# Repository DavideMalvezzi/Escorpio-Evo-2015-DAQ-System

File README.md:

# Introduction
Data Acquisition System realized for the prototype [Escorpio](https://www.facebook.com/TeamZeroCEscorpioEvo/?fref=ts) in 2015.

The DAQ System was realized to get real-time information from the prototype Escorpio during its races and visualize the data on a PC through
charts and widgets.

In the **HW** folder are placed the electronics boards realized with eagle. All the boards where controlled by an Arduino Due and placed inside 
the prototype.

In the **SW** folder are placed the software sources file:
- the Arduino Due software was in charge of collecting all the prototype data through the [Can Bus](https://en.wikipedia.org/wiki/CAN_bus) inside Escorpio and then to send the data 
to a remote PC using a [GSM SIM 900 module](http://www.geeetech.com/wiki/index.php/Arduino_GPRS_Shield);
- the remote PC was connected to another GSM SIM 900 module via USB and the software was in charge of controlling it, parse all the data 
coming from the other module and show it with charts and widgets. All the visualization views are completely personalizable thanks to the
user interface. All the data received is also saved in a local SQLite database.

All the code is C++, using [Qt Library](https://www.qt.io/developers/) for the PC software.

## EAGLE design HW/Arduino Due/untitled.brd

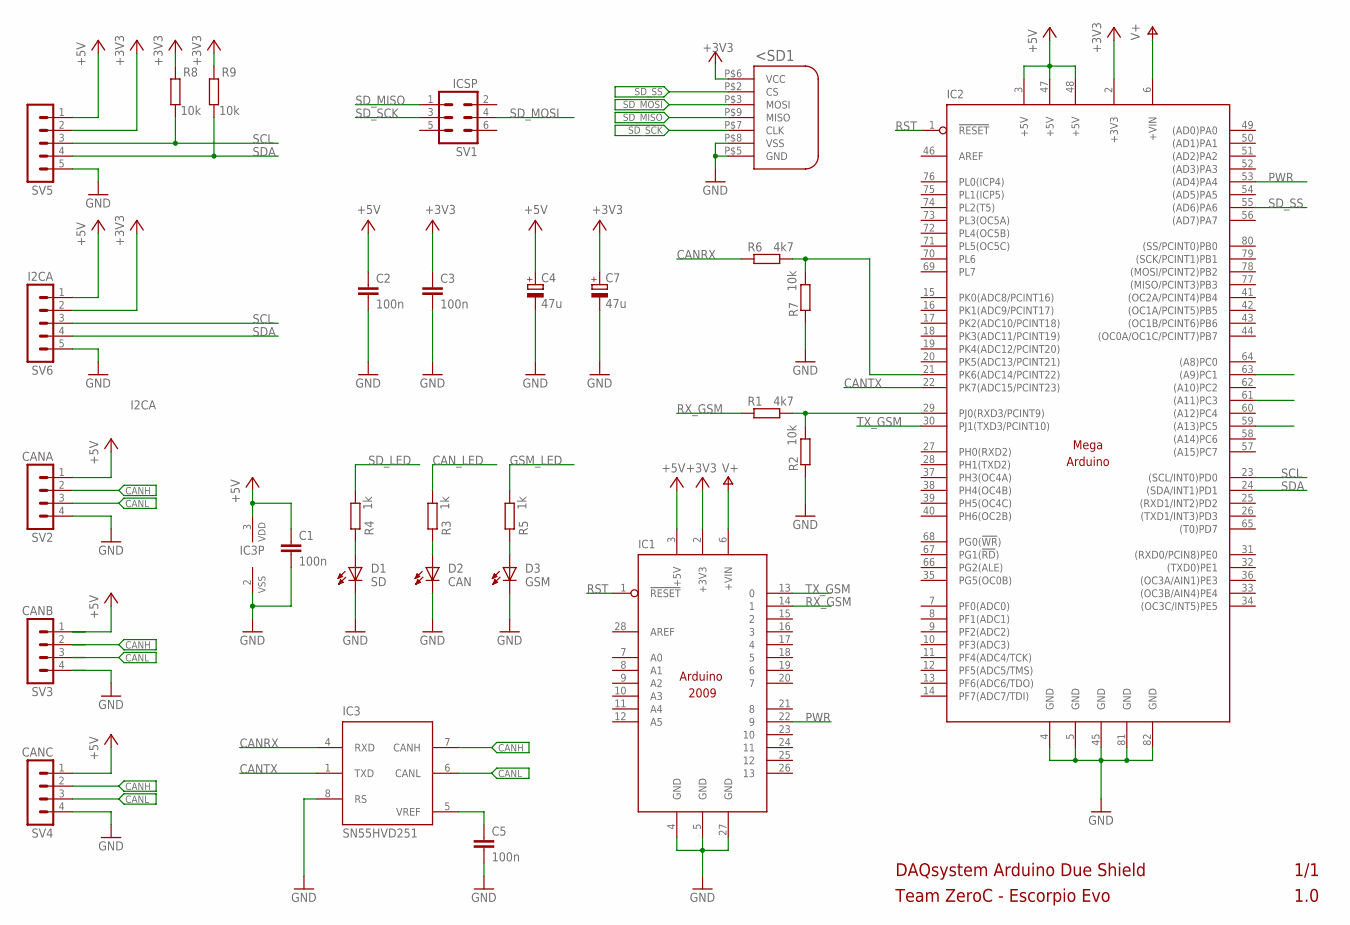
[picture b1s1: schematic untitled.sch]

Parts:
C1, C2, C3, C5: 100n; C3225
C4, C7: 47u; E-01
D1: SD; LED5MM
D2: CAN; LED5MM
D3: GSM; LED5MM
IC1: ARDUINO2009_10; ARDUINO2009
IC2: MEGAARDUINO_1; MEGA_ARDUINO
IC3: SN55HVD251; DIL8
R1, R6: 4k7; M1206
R2, R7, R8, R9: 10k; M1206
R3, R4, R5: 1k; M1206
SV1: ICSP; MA03-2
SV2: CANA; MA04-1
SV3: CANB; MA04-1
SV4: CANC; MA04-1
SV5, SV6: I2CA; MA05-1
U$2: SD_CARD; SD

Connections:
+3V3: C3.1, C7.+, IC1.2 (+3V3), IC2.2 (+3V3), R8.2, R9.2, SV5.2, SV6.2, U$2.P$6 (VCC)
+5V: C1.1, C2.1, C4.+, IC1.3 (+5V), IC2.3 (+5V), IC2.47 (+5V), IC2.48 (+5V), IC3.3 (VDD), SV2.1, SV3.1, SV4.1, SV5.1, SV6.1
CANH: IC3.7 (CANH), SV2.2, SV3.2, SV4.2
CANL: IC3.6 (CANL), SV2.3, SV3.3, SV4.3
CANRX: IC3.4 (RXD), R6.2
CANTX: IC2.22 (PK7(ADC15/PCINT23)), IC3.1 (TXD)
CAN_LED: IC2.63 ((A9)PC1), R3.1
GND: C1.2, C2.2, C3.2, C4.-, C5.2, C7.-, D1.K (C), D2.K (C), D3.K (C), IC1.4 (GND), IC1.5 (GND), IC1.27 (GND), IC2.4 (GND), IC2.5 (GND), IC2.45 (GND), IC2.81 (GND), IC2.82 (GND), IC3.2 (VSS), IC3.8 (RS), R2.2, R7.2, SV2.4, SV3.4, SV4.4, SV5.5, SV6.5, U$2.P$5 (GND), U$2.P$8 (VSS)
GSM_LED: IC2.61 ((A11)PC3), R5.1
unnamed: IC2.21 (PK6(ADC14/PCINT22)), R6.1, R7.1
unnamed: IC2.29 (PJ0(RXD3/PCINT9)), R1.1, R2.1
unnamed: D2.A, R3.2
unnamed: D3.A, R5.2
unnamed: C5.1, IC3.5 (VREF)
unnamed: D1.A, R4.2
PWR: IC1.22 (9), IC2.53 ((AD4)PA4)
RST: IC1.1 (!RESET), IC2.1 (!RESET)
RX_GSM: IC1.14 (1), R1.2
SCL: IC2.23 ((SCL/INT0)PD0), R8.1, SV5.3, SV6.3
SDA: IC2.24 ((SDA/INT1)PD1), R9.1, SV5.4, SV6.4
SD_LED: IC2.59 ((A13)PC5), R4.1
SD_MISO: SV1.1, U$2.P$9 (MISO)
SD_MOSI: SV1.4, U$2.P$3 (MOSI)
SD_SCK: SV1.3, U$2.P$7 (CLK)
SD_SS: IC2.55 ((AD6)PA6), U$2.P$2 (CS)
TX_GSM: IC1.13 (0), IC2.30 (PJ1(TXD3/PCINT10))
V+: IC1.6 (+VIN), IC2.6 (+VIN)

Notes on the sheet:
DAQsystem Arduino Due Shield
Team ZeroC - Escorpio Evo
1/1
1.0

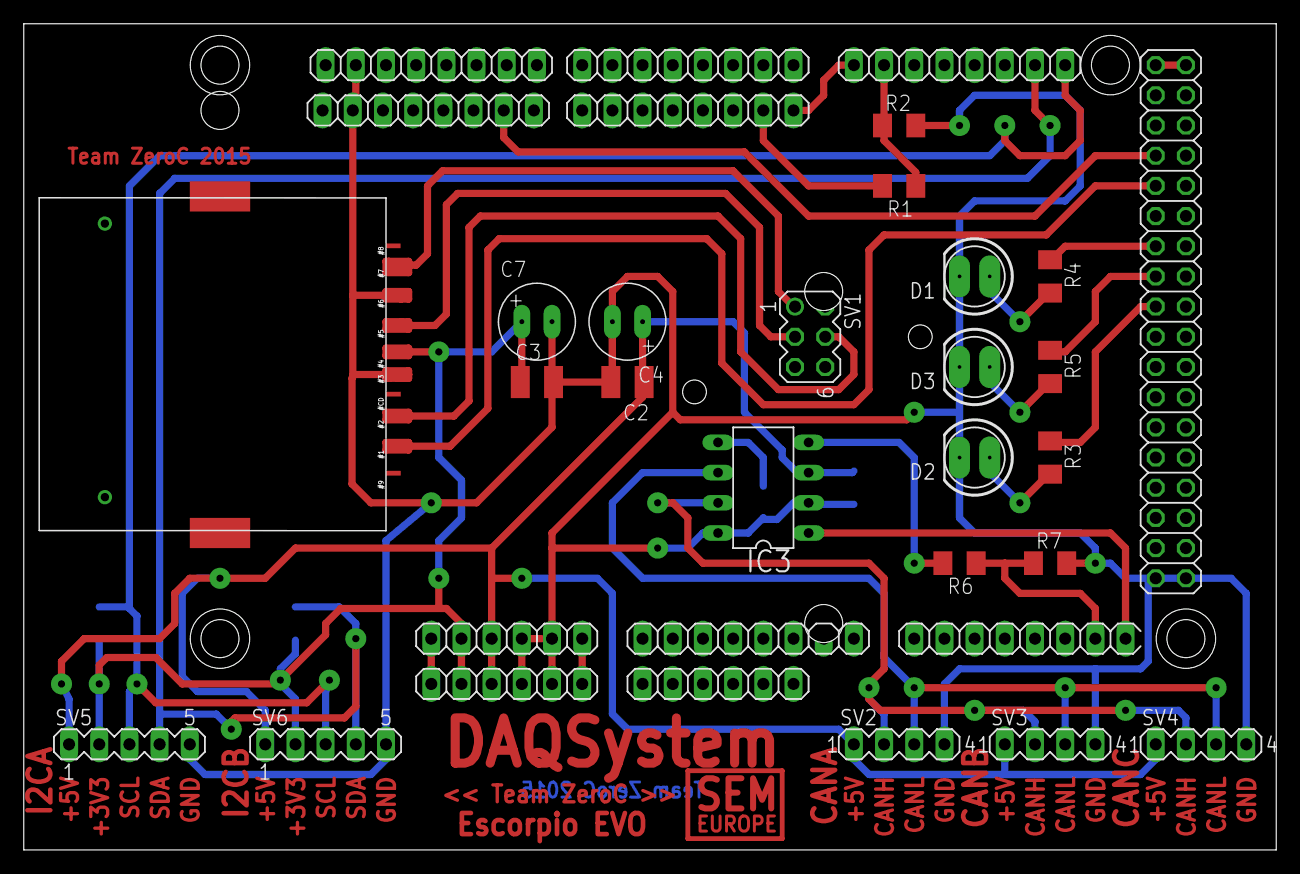
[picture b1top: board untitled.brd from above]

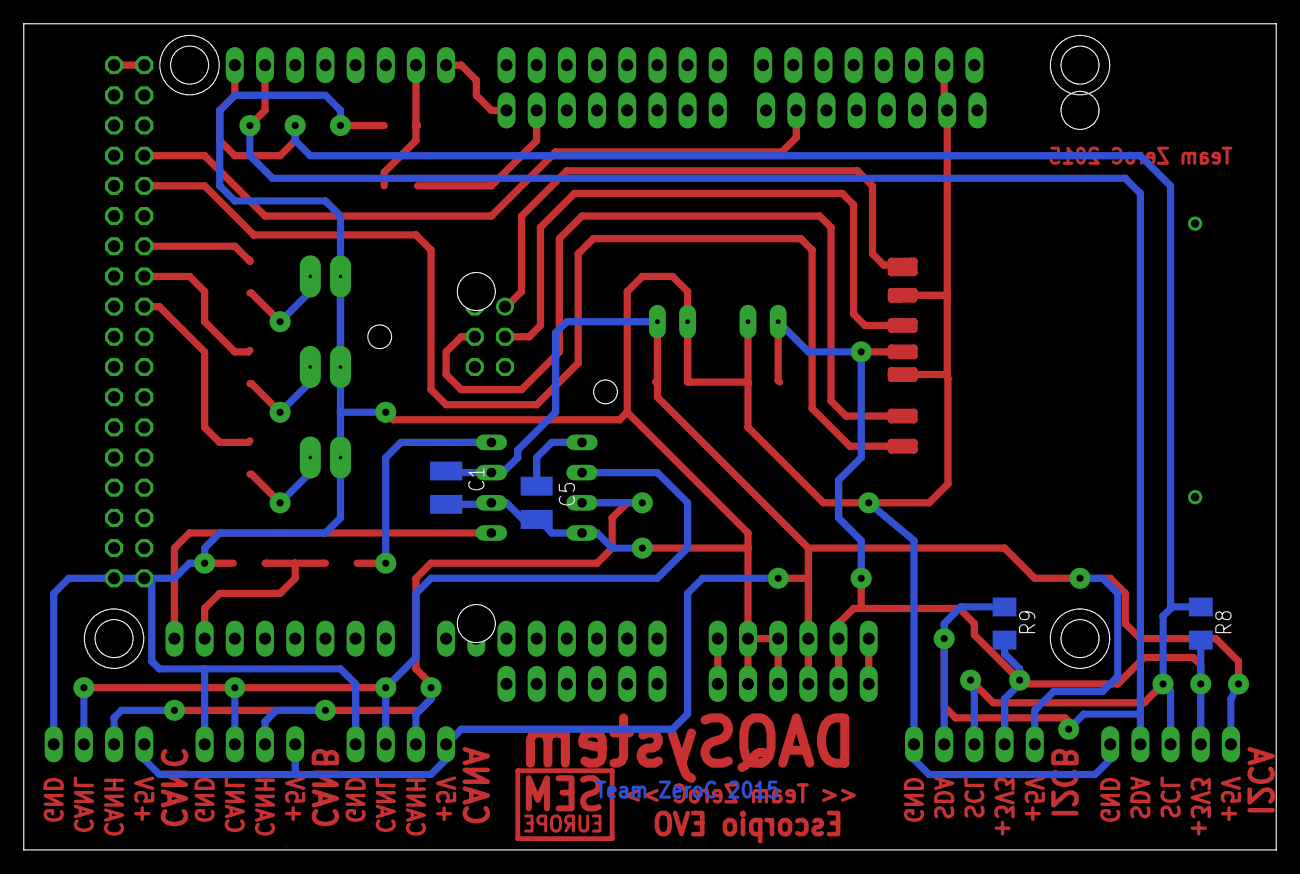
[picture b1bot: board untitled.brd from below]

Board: 2 copper layers, 105.4 x 69.5 mm, 28 parts (4 on the bottom side), 27 nets.

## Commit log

2016-05-30 :octocat: Added .gitattributes & .gitignore files
2016-05-30 Added docs
    Backup docs
2016-05-30 Added HW layout
    Added HW layout
2016-05-30 Added Arduino Due code
    Added Arduino Due code
2016-05-30 Added DAQ Recorder code
    Added DAQ Recorder code
2016-05-30 Added dlls
    Added dlls
